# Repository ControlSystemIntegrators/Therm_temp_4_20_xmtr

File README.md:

# Analog 4–20 mA Thermistor Temperature Transmitter

A fully **analog** (no microcontroller) 2-wire 4–20 mA temperature transmitter
built from **standard, multi-sourced parts** — and a worked tutorial in the
instrumentation theory behind it.

It does two jobs:

1. **A teaching reference.** If you've ever wanted to understand how a 4–20 mA
   transmitter actually works — loop power, sensor excitation, linearization,
   zero/span calibration — this is a complete, honest, end-to-end example with
   the math shown and a calculator you can run.
2. **A real instrument.** It was designed for **chocolate temperature control**
   (the 20–40 °C tempering/working range), as a more accurate and more robust
   replacement for thermocouples. But it is parameterized: point the included
   calculator at *your* thermistor and *your* temperature band and it tells you
   which resistors to fit.

> **Why analog?** You can absolutely bolt a microcontroller and a 12-bit ADC on
> top of this for fine digital adjustment — see [Optional digital
> upgrade](#optional-digital-upgrade). In practice, for "hold a setpoint in a
> known band" process control, that layer is rarely worth the complexity. This
> project deliberately stays in the analog domain so the whole signal path is
> visible and every part is replaceable.

> **Not a safety device.** This is a process measurement instrument, not a
> safety-rated (SIL) one. Don't use it as a protective function.

---

## Specifications (default build)

| Parameter | Value |
|---|---|
| Output | 4–20 mA, 2-wire loop-powered |
| Loop supply | 7–30 V (24 V typical) |
| Default range | **20–40 °C → 4–20 mA** (chocolate) |
| Sensor | NTC thermistor, 10 kΩ @ 25 °C, β ≈ 3892 K (e.g. Omega 44006) |
| In-band accuracy | **±0.1 °C over the 20 °C band** (realistic system figure; the electronics + linearization contribute only ~±0.06 °C — sensor interchangeability, self-heating and lead effects dominate) |
| Calibration | zero + span trimpots, non-interactive |
| Quiescent current | ~2.6 mA (fits under the 4 mA floor) |
| Components | jellybean / multi-sourced; op-amps in SOT-23-5 |

Outside the chosen band the output saturates near 4 mA (cold) or 20 mA (hot) —
intentional. Accuracy is only specified inside the band.

---

## How a 4–20 mA transmitter works (the theory)

**The current loop.** A 2-wire transmitter sits in series with a DC supply and
a receiver. The transmitter's job is to *draw a controlled current* from the
loop — 4 mA represents the bottom of the range, 20 mA the top — regardless of
loop voltage or wiring resistance (within limits). Because the *current* is the
signal, voltage drops in long cable runs don't corrupt the reading, and a broken
wire reads 0 mA (a detectable fault, distinct from a valid 4 mA "low"). That
noise immunity and fault detection is why 4–20 mA has survived for decades in
industry.

**Loop-powered ("2-wire").** The same two wires that carry the signal also power
the transmitter. The catch: the *entire* circuit must run on **less than 4 mA**,
because that floor is the lowest the loop ever provides. Every microamp the
electronics draw is part of the loop current, so the design budgets quiescent
current carefully and lets an output ("dump") transistor make up the difference
to hit the commanded 4–20 mA.

**Why a thermistor?** An NTC thermistor is cheap, has a large signal (thousands
of ohms change over our band), is available with tight interchangeability
(±0.1–0.2 °C for the Omega 44000 series), and needs no cold-junction
compensation like a thermocouple. Its one drawback is that it is **very
nonlinear** — which is the interesting part of this design.

---

## The nonlinearity problem (and the one-resistor fix)

An NTC's resistance is approximately

```
R(T) = R25 · exp( β · (1/T − 1/298.15) )      [T in kelvin]
```

For our 10 kΩ part that's ~57 kΩ at −10 °C falling to ~3.6 kΩ at +50 °C — about
15:1, and badly curved. Fed straight into a linear amplifier you'd get large
errors away from one calibration point.

**The fix is a single resistor in parallel with the thermistor.** The parallel
combination `Rt ∥ Rlin` has an S-shaped curve with an inflection point; placing
that inflection at the *center* of your band makes the network resistance very
nearly linear in temperature there. The value for maximum linearity at center
temperature `Tc` (kelvin) is:

```
Rlin = Rt(Tc) · (β − 2·Tc) / (β + 2·Tc)
```

For the chocolate build (center 30 °C) the closed-form (unloaded) value is
~5.9 kΩ; the build uses **6.04 kΩ**, re-optimized for the gain-stage loading
(see [below](#dont-let-the-gain-stage-load-the-sensor)). Either way the residual
nonlinearity across 20–40 °C is only ~**±0.06 °C** — comfortably inside the
±0.1 °C system spec, so the linearization is never the limiting term.

### Why one resistor and not two

A second resistor *can* add a curvature-shaping term (by exciting through a
divider instead of a constant current), so we checked whether it's worth it.
For an NTC it essentially isn't — the optimizer drives the second resistor back
toward "constant current," and the conformity barely moves:

| Band → 4–20 mA | 1 resistor | 2 resistors |
|---|---|---|
| 20–40 °C | ±0.061 °C | ±0.057 °C |
| 15–45 °C | ±0.207 °C | ±0.188 °C |
| −10–50 °C | ±1.585 °C | ±1.545 °C |

~5% improvement for an extra precision part and an extra calibration
interaction. We dropped it. **The real lever is band width, not resistor count**
(see the table — the wider the band, the worse the conformity). Pick the
narrowest band that covers where your process actually operates.

### Don't let the gain stage load the sensor

There's a subtle trap the ideal math hides. The single-op-amp difference amp
(next stage) presents its input network — `R9 + R12` from the sensor node to
ground — as a *load* on node X. The sensor's source impedance there is the
linearized network (a few kΩ), so a low input impedance bleeds a
temperature-dependent current out of the node and **bows V(X)**, adding
nonlinearity the zero/span trims cannot remove.

We only caught this with the **device-level SPICE model** (the ideal netlist and
the first cut of `design.py` both assumed an infinite-impedance gain input). With
the original 10 k / 24.9 k divider (`R9+R12 ≈ 35 kΩ`) loading a ~4 kΩ source, the
in-band conformity blew out to **±0.18 °C** — past the spec. Two fixes, both
verified:

1. **Raise the gain-stage input impedance** so it stops loading the node — this
   build uses `R9=R10=100 kΩ`, `R11=R12=249 kΩ` (`R9+R12 ≈ 349 kΩ`, ~1 % loading).
2. **Re-optimize R1** for whatever loading remains — `design.py` now models the
   load (`--rload`) and searches for the best linearization resistor rather than
   trusting the unloaded closed form (hence 6.04 kΩ, not 5.9 kΩ).

With both, conformity is back to **±0.058 °C**, confirmed in the device-level
sim. Lesson: a difference amp driven from a non-trivial source impedance must
have an input impedance well above it, or you pay for it in linearity.

You can reproduce all of this — and design for your own sensor/range — with
[`tools/design.py`](tools/design.py).

---

## Circuit overview

Two views: the **signal chain** (what computes the current) and the
**power/output loop** (how a 2-wire device powers itself and sets loop current).

### Signal chain

```
 Vref(2.5V) ──[ NTC ∥ Rlin ]──● X ─────────────►┌────────────┐
                              │                 │   A2       │
              A1 sinks Iexc ──┘                 │ gain/zero  │─ Vcmd ─►┌──────────┐
              (0.25 mA, constant)               │  (2 pots)  │         │ A3 servo │─► loop
                                                └────────────┘         │  + Q2    │   current
   V(X) = Vref − Iexc·(NTC ∥ Rlin)                                     └──────────┘
        (rises with temperature)        Vcmd = SPAN·(V(X) − ZERO)   Iloop = Vcmd / Rsense
```

A constant current is pulled through the linearized network, so the node voltage
`V(X)` is a clean, near-linear function of temperature. The gain/zero amplifier
scales and offsets it; the output stage turns that command voltage into loop
current.

### Power / output loop

```
 LOOP+ ──▷|──┬───────────────────────────────┬──────────► IN (raw 7..30 V)
   (24 V) D1 │                               │
           TVS         pre-reg: Q1 + TL431 ───┤────────► VL (+5 V) ─► Vref, A1, A2, A3
            │          (series NPN follower)  │
            │                                 └────────► Q2 collector (dump)
            │                                                  │ emitter
 LOOP- ─────┴────────────────[ Rsense 50Ω ]──────  AGND ───────┘
                                    ▲
                A3 drives Q2 so that  Iloop · Rsense = Vcmd
```

Everything returns to `AGND` and flows out through `Rsense`, so the
sense resistor sees the **total** loop current — the electronics' own ~2.6 mA
quiescent draw plus whatever the dump transistor `Q2` adds. A3 servos `Q2` until
that total equals `Vcmd / Rsense`. Because quiescent draw (~2.6 mA) is below the
4 mA floor, `Q2` always has something to add.

### Stage-by-stage

| Stage | Parts | Function | Key relation |
|---|---|---|---|
| Protection | D1 (Schottky), TVS | reverse-polarity + surge | — |
| Pre-regulator | Q1 (NPN follower), TL431, divider, + Q4/Q5 bias source | makes the +5 V rail `VL` from the loop; **series** pass, not shunt, so it draws only what the electronics need. Q4/Q5 form a 2-transistor constant-current source (a jellybean replacement for a current-regulating diode) that biases the TL431 flat across the 7–30 V loop | `VL = 2.5·(1+Rfa/Rfb)` |
| Reference | LM4040-2.5 | 2.500 V for excitation + zero | — |
| Excitation | A1, Q3, Rexc | constant `Iexc = Vref/Rexc = 0.25 mA` pulled through `NTC∥Rlin` | `V(X)=Vref − Iexc·Rnet` |
| Linearization | Rlin (6.04 kΩ) | straighten the curve in-band | `Rlin = Rt(Tc)·(β−2Tc)/(β+2Tc)`, re-optimized for load |
| Gain/Zero | A2 + **span pot** + **zero pot** | scale & offset to the command voltage | `Vcmd = SPAN·(V(X) − ZERO)` |
| Output | A3, Q2, Rsense | servo loop current to the command | `Iloop = Vcmd / Rsense` |

> **The three knobs are orthogonal**, which makes calibration sane:
> **Rlin** depends only on the band *center*, **span** on the band *width*, and
> **zero** on the band *position*. Move the band up/down → re-zero only. Widen
> it → re-span only. Re-center it → change Rlin.

---

## Selecting components for your own range

Run the calculator with your sensor and the two temperatures you want at 4 mA
and 20 mA:

```
python3 tools/design.py --r25 10000 --beta 3892 --tlow 20 --thigh 40
```

It prints the linearization resistor, the excitation resistor, the span (gain)
and zero (offset) targets, the conformity error you'll get, the self-heating
estimate, and a transfer table. Defaults are the chocolate build. Output for the
default:

```
--- Linearization ---
Rlin (E96)      : 6.040 kohm   <- re-optimized for gain-stage loading
Conformity      : +/- 0.059 C
--- Excitation ---
Rexc (E96)      : 10.000 kohm  -> Iexc = 0.2500 mA
--- Amplifier / output stage ---
SPAN  (gain)    : 2.5706 V/V   <- set by span pot
ZERO  (Vzero)   : 1.3872 V     <- set by zero pot
```

**Manual recipe** (what the script does):

1. **Center → Rlin.** `Tc = (Tlow+Thigh)/2`; `Rlin = Rt(Tc)·(β−2Tc)/(β+2Tc)`,
   rounded to the nearest E96 value.
2. **Excitation.** Pick `Iexc` (~0.25 mA is a good balance of signal size vs.
   self-heating); set `Rexc = Vref / Iexc`.
3. **Edge voltages.** `V(X) = Vref − Iexc·(Rt ∥ Rlin)` at `Tlow` and `Thigh`.
4. **Span (gain).** `SPAN = (20mA−4mA)·Rsense / (V(X)@Thigh − V(X)@Tlow)`.
5. **Zero (offset).** Choose `ZERO` so the output is 4 mA at `Tlow`.

Then check the printed conformity. If it exceeds your target, your band is too
wide — narrow it (see the table above).

---

## Calibration

You need a way to present two known temperatures (a stirred ice/water-and-warm
bath, a dry-block calibrator, or — easiest for bench bring-up — **two precision
resistors** substituted for the probe equal to `Rt(Tlow)` and `Rt(Thigh)`, which
the calculator prints).

1. Apply the **low** point (`Tlow`, e.g. 20 °C → `Rt = 12.49 kΩ`). Adjust the
   **ZERO** pot for **4.00 mA**.
2. Apply the **high** point (`Thigh`, e.g. 40 °C → `Rt = 5.35 kΩ`). Adjust the
   **SPAN** pot for **20.00 mA**.
3. Repeat once. Zero and span interact only slightly (the gain term scales the
   zero point a little), so a second pass nails both to within a microamp.

Use a loop calibrator or a 250 Ω precision resistor + DMM (1.000–5.000 V = 4–20
mA) to read the current.

---

## Bill of materials (multi-sourced)

Every active part below is available from multiple manufacturers, or in a
footprint with many drop-in alternatives. That is a design goal: this instrument
should be repairable for decades without a single-source IC.

| Ref | Part | Function | Second-source notes |
|---|---|---|---|
| RT1 | NTC 10 kΩ, β≈3892 (Omega 44006 / equiv.) | sensor | any 10k NTC with known β; re-run calculator for other betas |
| Rlin | 6.04 kΩ, 1%, ≤25 ppm/°C | linearization | passive, universal |
| U1 | LM4040-2.5 (2.500 V) | reference | TI, ADI, Diodes, ON |
| U2 | TL431 (2.5 V shunt ref) | pre-reg reference | TI, ON, Diodes, ST, UTC — *the* multi-sourced jellybean; KiCad sym `TL431DBZ` (SOT-23) |
| Q1 | NPN small-signal (MMBT3904 / BC847) | pre-reg pass (follower) | universal |
| Q2 | NPN, ~0.5 W (SOT-223, e.g. BCP56 / PZTA42) | output dump transistor | universal; **see thermal note** |
| Q3 | NPN small-signal (MMBT3904 / BC847) | excitation current sink | universal |
| A1–A3 | µpower precision op-amp, **SOT-23-5** (OPA333 / MCP6V31 / TLV9061-class) | excitation, gain/zero, output servo | by exact PN limited; by SOT-23-5 footprint, dozens of swappable parts |
| Rexc | 10.0 kΩ, 1%, ≤25 ppm/°C | sets Iexc | passive |
| Rsense | 49.9 Ω (or 50 Ω), 1%, ≤25 ppm/°C | loop sense | passive |
| Rfa/Rfb | 10.0 kΩ / 10.0 kΩ, 1% | sets VL = 2.5·(1+Rfa/Rfb) = 5 V | passive |
| RV1 | zero trim, SMD multiturn cermet (e.g. 3269 / 3224) | ZERO | universal |
| RV2 | span trim, SMD multiturn cermet | SPAN | universal |
| D1 | Schottky SMA (SS14 / BAT54) | reverse polarity | universal |
| TVS1 | SMAJ33A (or per supply) | surge | universal |
| C1–Cn | 100 nF + 1–10 µF bypass | decoupling | universal |

**Thermal note (Q2).** A 2-wire transmitter must drop the loop voltage somewhere;
that's Q2. Worst case ≈ (instrument voltage) × (loop current) ≈ 20 V × 20 mA ≈
**0.4 W**. Use a SOT-223 (or larger) device with adequate copper, or split the
drop with a series resistor ahead of Q2's collector.

**Op-amp footprint.** Standardizing A1–A3 on **SOT-23-5 singles** is deliberate:
precision op-amps are mostly single-source by part number, but the SOT-23-5
single-op-amp pinout is a de-facto industry standard with many footprint-
compatible options, so a substitute is always a re-qualification away, never a
redesign.

---

## Simulation

[`sim/transmitter.cir`](sim/transmitter.cir) models the ideal signal chain
(reference + op-amps as behavioral sources, NTC as a temperature-dependent
resistor) and DC-sweeps temperature to confirm the 4–20 mA transfer and in-band
linearity.

```
ngspice -b sim/transmitter.cir   # DC-sweeps temperature; prints Iloop vs T
```

(LTspice: change the behavioral-resistor `r='...'` syntax to `R=...`.)

It has been run with **ngspice 46**; the full output is saved in
[`sim/SIM_RESULTS.txt`](sim/SIM_RESULTS.txt). Key points (Iloop = Vcmd / 50 Ω):

| T (°C) | V(x) | Vcmd | Iloop |
|---|---|---|---|
| 20 | 1.49812 V | 0.20009 V | **4.00 mA** |
| 30 | 1.64825 V | 0.59996 V | **12.00 mA** |
| 40 | 1.79854 V | 1.00024 V | **20.00 mA** |
| <20 | — | clamps 0.190 V | 3.8 mA (under-range) |
| >40 | — | clamps 1.025 V | 20.5 mA (over-range) |

The node voltages match `tools/design.py` to the millivolt, and the in-/out-of-
band clamping behaves as designed.

**Verification status (be honest about it):**

- ✅ Signal-chain transfer and linearization conformity (~**±0.06 °C**, well
  inside the **±0.1 °C** system spec) — verified in `tools/design.py` **and
  confirmed in ngspice** (table above).
- ⬜ Discrete output stage (the Q1 pre-regulator and the Q2/A3 servo loop,
  including loop stability and Q2 thermals) — **designed but not yet
  device-level simulated or bench-verified.** The netlist above models the
  op-amps as ideal behavioral sources, so it validates the *transfer math*, not
  the real parts. Simulate with device models and prototype before trusting it.

---

## Optional digital upgrade

If you later want digital trim, datalogging, or a nonlinear curve over a wide
range, you can add an MCU with a ≥12-bit ADC reading `V(X)` and driving the loop
via a current-output DAC (or by replacing the A3/Q2 stage). For a "hold a
setpoint in a known band" application this is usually unnecessary complexity —
the analog path here already beats thermocouple accuracy in-band — but the
sensor front-end and linearization theory carry over unchanged.

---

## Working with KiCad — notes and gotchas

Taking this from netlist to schematic to PCB surfaced a few KiCad limitations
worth recording — both for anyone reproducing the board and for anyone doing a
careful (or AI-assisted) review of a `.kicad_sch`:

- **Connectivity can't be read reliably from the `.kicad_sch` text.** Symbol
  mirror/rotation transforms and overlapping wire segments defeat any attempt to
  infer "what's connected to what" from pin coordinates. Let KiCad compute it
  instead — `kicad-cli sch export netlist --format kicadsexpr -o net.net
  therm.kicad_sch` — and read the nets. Every net-by-net review of this board was
  done that way, not by eyeballing the schematic file.

- **ERC does not catch wrong *values* or wrong *roles*.** Several real errors
  here passed connectivity checks clean: a `49.9 kΩ` loop-sense resistor that
  should have been `49.9 Ω`; a bypass cap with *both* pins on the same net (a
  no-op); an op-amp powered from the 2.5 V reference instead of the 5 V rail; and
  the LM4040 reference wired across the loop input as if it were the TVS. None of
  these trip ERC — they need an explicit value-and-node audit against intent.

- **Symbol variants have different pin numbering.** The OPA333 in SOIC-8
  (`OPA333xxD`) uses pins 2/3/4/6/7; in SOT-23-5 (`OPA333xxDBV`) it's 1–5. Grab
  the wrong variant and the schematic *looks* right while the netlist is wrong —
  always confirm the symbol's package/pinout matches the footprint you intend.

- **Not every jellybean part is in the stock library.** The TL431 is
  (`Reference_Voltage:TL431DBZ`); the TLV431 is not, which had forced a custom
  symbol — one reason we standardized on the TL431. Preferring stock-library
  parts avoids custom-symbol upkeep.

- **Footprints aren't auto-assigned.** Symbols sit with an empty footprint until
  you assign one, and nothing warns you until you try to lay out the board — the
  two trimpots were caught this way. Sweep for missing footprints before routing.

- **File hygiene.** KiCad scatters `*-backups/` zips, `~*.lck` locks,
  `#auto_saved_files#`, and per-user `*.kicad_prl` state through the project; the
  [`.gitignore`](.gitignore) excludes them so only the real design files track.

**Takeaway:** a parameterized calculator proves the design *intent*, and ERC
proves the nets are *connected* — but neither flags a wrong value, a wrong
package variant, or a node that's electrically valid yet functionally pointless.
A net-by-net netlist review plus a device-level SPICE pass are what actually
prove the *instrument*.

---

## Repository layout

```
Therm_temp_4_20_xmtr/
├── README.md                    # this file
├── LICENSE                      # MIT
├── docs/
│   └── DESIGN_CONVERSATION.md   # the prompts that drove the design + decisions
├── hardware/
│   └── BOM.md                   # bill of materials (consolidated values, tempco notes)
├── tools/
│   └── design.py                # parameterized design calculator (models gain-stage load)
├── sim/
│   ├── transmitter.cir          # ideal transfer-function verification
│   ├── device_level.cir         # discrete model (real BJTs + IC macromodels)
│   └── SIM_RESULTS.txt          # captured ngspice 46 output
└── therm_kicad/                 # KiCad project: schematic + rough PCB
    └── therm/                   # therm.kicad_sch / .kicad_pcb / .kicad_pro
```

For *how* this design came to be — the design conversation and the reasoning
behind each choice — see [`docs/DESIGN_CONVERSATION.md`](docs/DESIGN_CONVERSATION.md).

Status: schematic + a rough PCB are in `therm_kicad/`; the device-level SPICE
model verifies the discrete signal chain. Still open: output-stage **loop
stability** (AC/transient) and **bench bring-up**.

## License

[MIT](LICENSE). Use it, build it, sell it — just keep the copyright notice.

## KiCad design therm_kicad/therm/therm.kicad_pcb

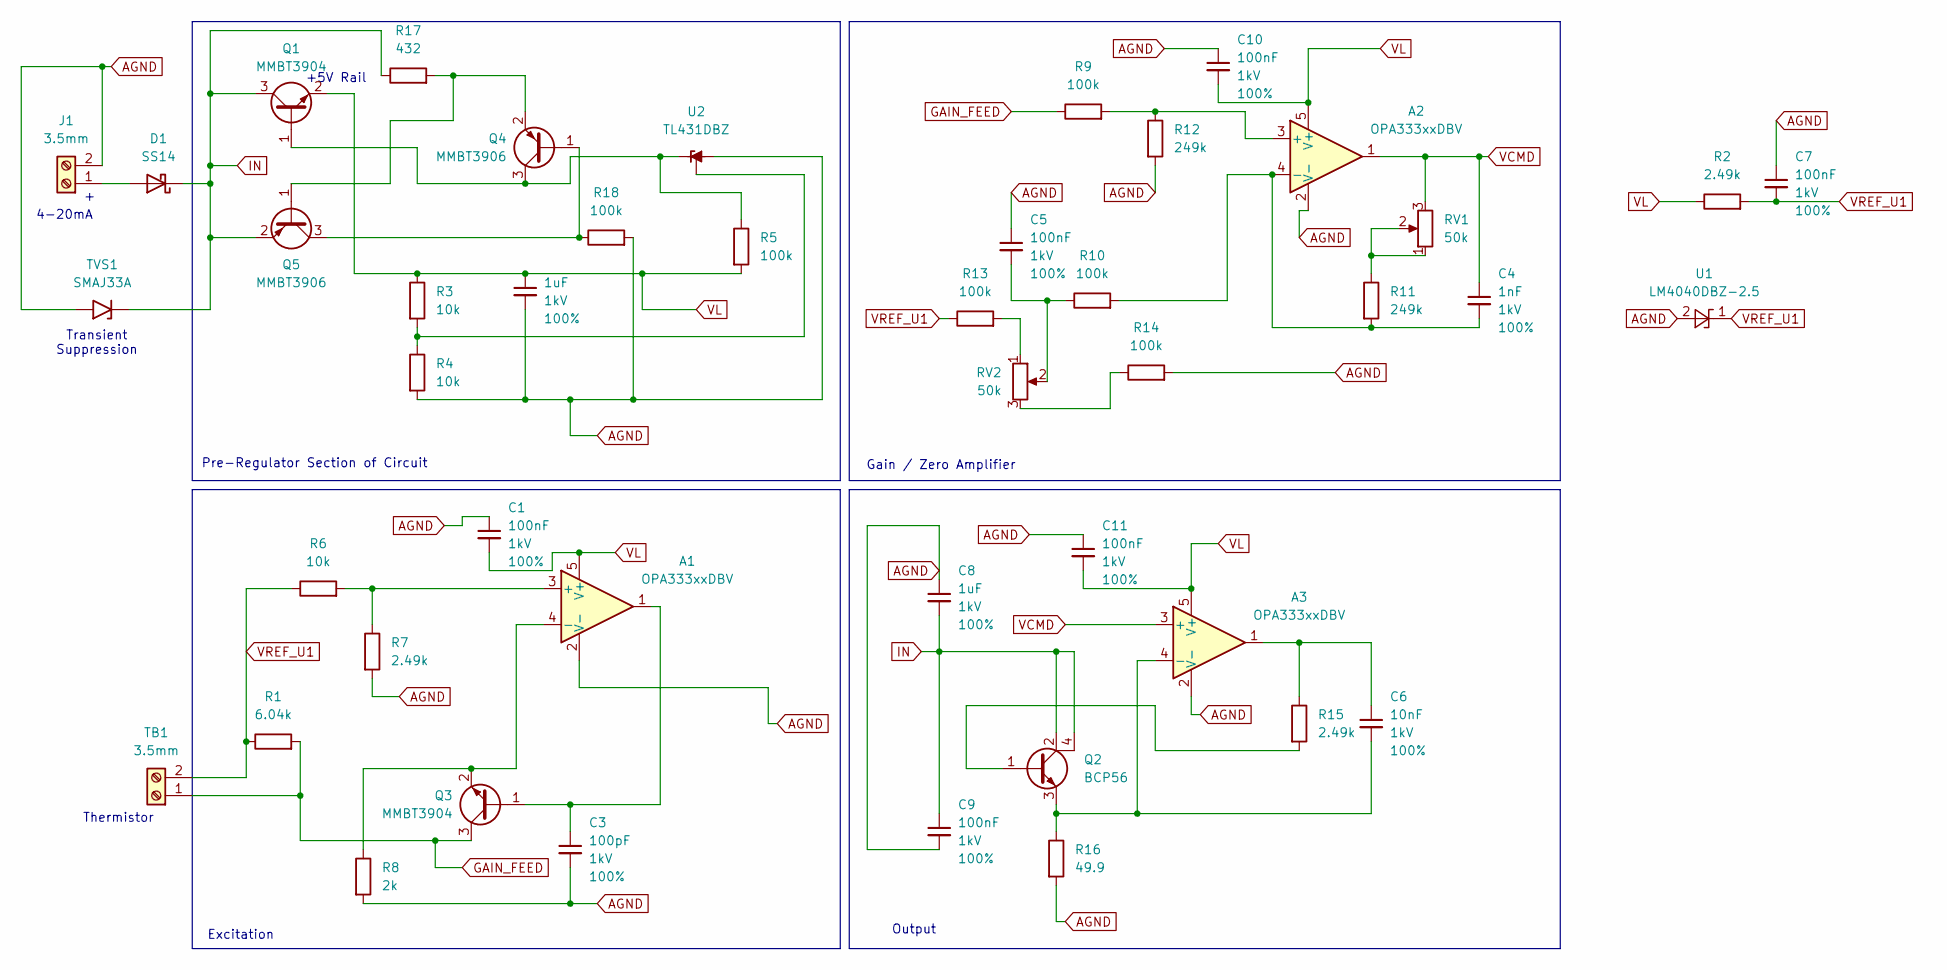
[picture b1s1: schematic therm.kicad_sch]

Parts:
A1, A2, A3: OPA333xxDBV; SOT-23-5
C1, C5, C7, C9, C10, C11: 100nF; C_0603_1608Metric; Voltage 1kV; Tolerance 100%
C2, C8: 1uF; C_0603_1608Metric; Voltage 1kV; Tolerance 100%
C3: 100pF; C_0603_1608Metric; Voltage 1kV; Tolerance 100%
C4: 1nF; C_0603_1608Metric; Voltage 1kV; Tolerance 100%
C6: 10nF; C_0603_1608Metric; Voltage 1kV; Tolerance 100%
D1: SS14; D_SMA
J1: 3.5mm; ScrewTerminal_1x02_P3.5mm_Horizontal_Black
Q1, Q3: MMBT3904; SOT-23
Q2: BCP56; SOT-223-3_TabPin2
Q4, Q5: MMBT3906; SOT-23
R1: 6.04k; R_0603_1608Metric
R2, R7, R15: 2.49k; R_0603_1608Metric
R3, R4, R6: 10k; R_0603_1608Metric
R5, R9, R10, R13, R14, R18: 100k; R_0603_1608Metric
R8: 2k; R_0603_1608Metric
R11, R12: 249k; R_0603_1608Metric
R16: 49.9; R_0603_1608Metric
R17: 432; R_0603_1608Metric
RV1, RV2: 50k; Potentiometer_Bourns_3269W_Vertical
TB1: 3.5mm; ScrewTerminal_1x02_P3.5mm_Horizontal_Black
TVS1: SMAJ33A; D_SMA
U1: LM4040DBZ-2.5; SOT-23
U2: TL431DBZ; SOT-23

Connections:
AGND: A1.2 (V-), A2.2 (V-), A3.2 (V-), C1.1, C2.2, C3.2, C5.1, C7.1, C8.1, C9.2, C10.1, C11.1, J1.2, R4.2, R7.2, R8.2, R12.2, R14.2, R16.2, R18.2, TVS1.2 (A2), U1.2 (A), U2.3 (A)
GAIN_FEED: Q3.3 (C), R1.2, R9.1, TB1.1
IN: C8.2, C9.1, D1.1 (K), Q1.3 (C), Q2.2 (C), Q2.4 (C), Q5.2 (E), R17.1, TVS1.1 (A1)
unnamed: A1.3 (+), R6.2, R7.1
unnamed: A1.4 (-), Q3.2 (E), R8.1
unnamed: A2.3 (+), R9.2, R12.1
unnamed: A2.4 (-), C4.2, R10.2, R11.2
unnamed: A3.4 (-), C6.2, Q2.3 (E), R16.1
unnamed: A3.1, C6.1, R15.1
unnamed: C5.2, R10.1, RV2.2
unnamed: D1.2 (A), J1.1
unnamed: Q1.1 (B), Q4.3 (C), R5.1, U2.1 (K)
unnamed: Q2.1 (B), R15.2
unnamed: A1.1, C3.1, Q3.1 (B)
unnamed: Q4.1 (B), Q5.3 (C), R18.1
unnamed: Q4.2 (E), Q5.1 (B), R17.2
unnamed: R11.1, RV1.1, RV1.2
unnamed: R13.2, RV2.1
unnamed: R14.1, RV2.3
unnamed: R3.2, R4.1, U2.2 (REF)
VCMD: A2.1, A3.3 (+), C4.1, RV1.3
VL: A1.5 (V+), A2.5 (V+), A3.5 (V+), C1.2, C2.1, C10.2, C11.2, Q1.2 (E), R2.1, R3.1, R5.2
VREF_U1: C7.2, R1.1, R2.2, R6.1, R13.1, TB1.2, U1.1 (K)

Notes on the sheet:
4-20mA
Thermistor
Pre-Regulator Section of Circuit
Output
Transient Suppression
Excitation
+5V Rail
Gain / Zero Amplifier

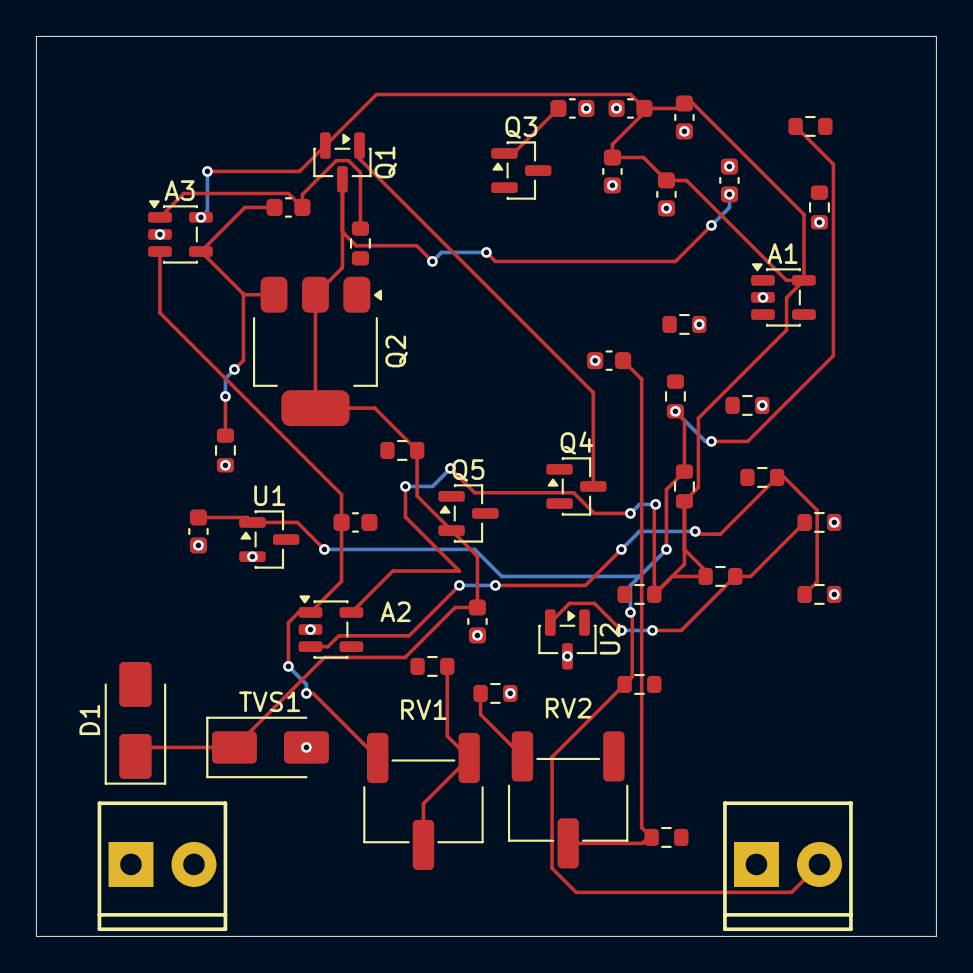
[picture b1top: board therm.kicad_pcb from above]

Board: 4 copper layers, 50.0 x 50.0 mm, 45 parts (0 on the bottom side), 23 nets.
